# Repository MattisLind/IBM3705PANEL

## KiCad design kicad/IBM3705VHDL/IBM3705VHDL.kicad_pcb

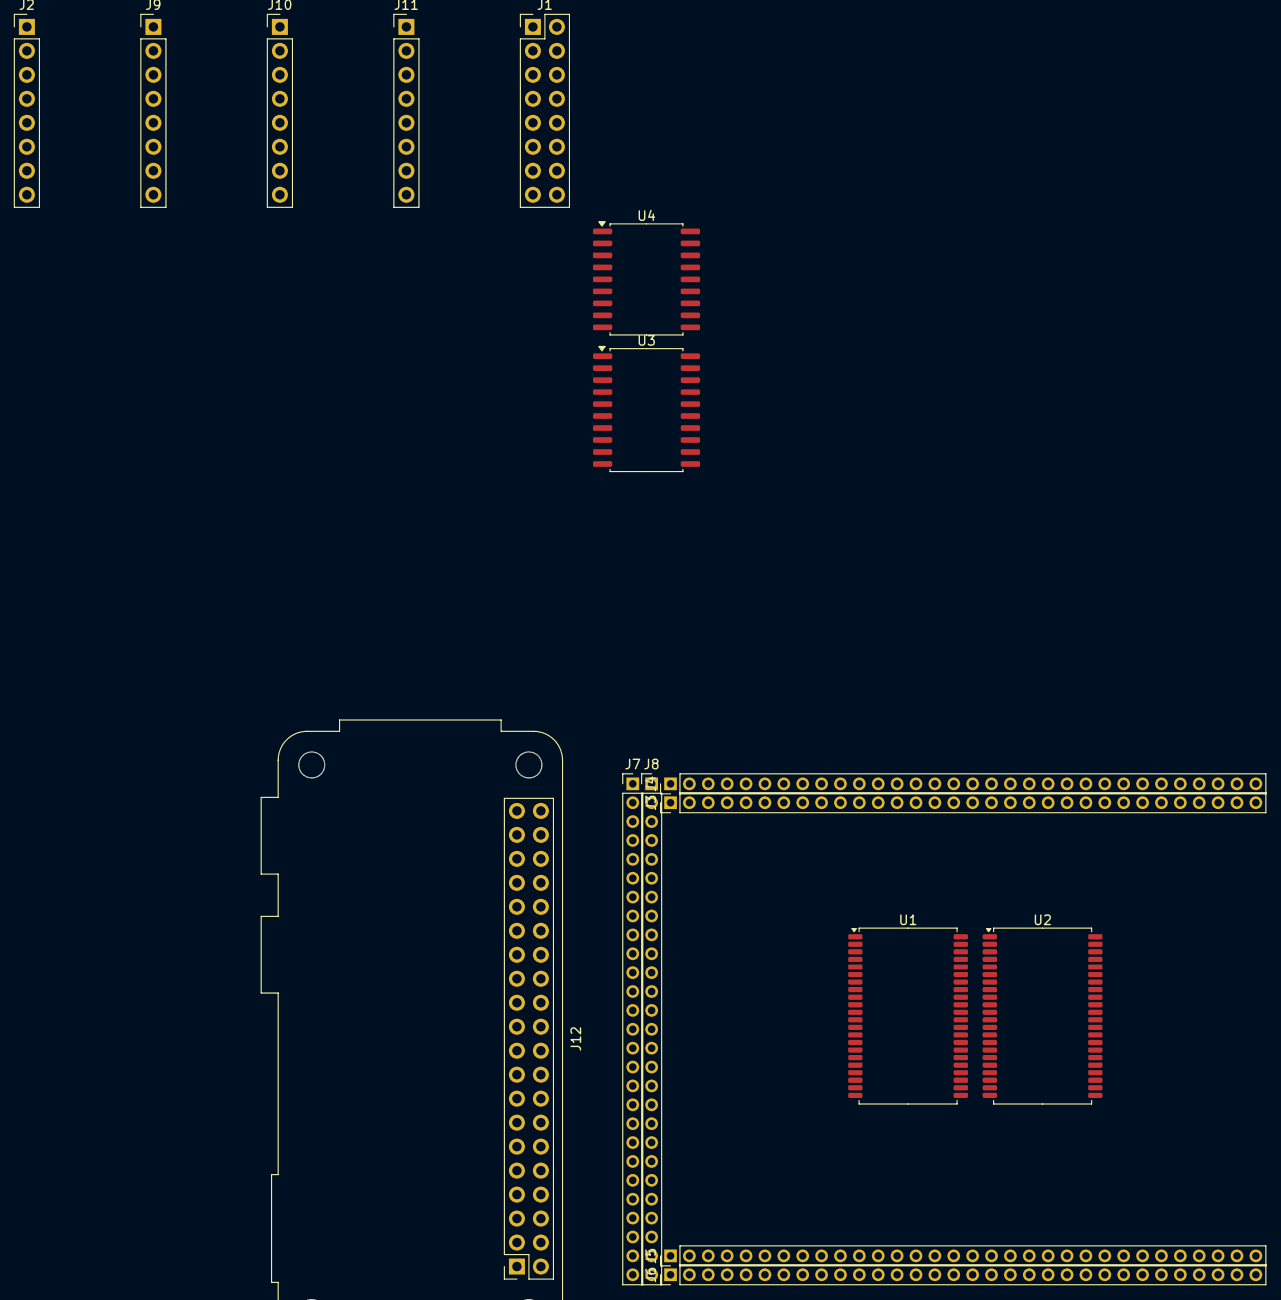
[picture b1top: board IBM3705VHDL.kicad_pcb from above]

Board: 2 copper layers, 16 parts (0 on the bottom side), 36 nets, no tracks yet.

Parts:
J1: Conn_02x08_Odd_Even; PinHeader_2x08_P2.54mm_Vertical
J2: Power; PinHeader_1x08_P2.54mm_Vertical
J3, J4, J5, J6: Conn_01x32; PinHeader_1x32_P2.00mm_Vertical
J7, J8: Conn_01x27; PinHeader_1x27_P2.00mm_Vertical
J9: 4V; PinHeader_1x08_P2.54mm_Vertical
J10: 6V; PinHeader_1x08_P2.54mm_Vertical
J11: 12V; PinHeader_1x08_P2.54mm_Vertical
J12: Raspberry_Pi_4; Raspberry_Pi_Zero_Socketed_THT_FaceDown_MountingHoles
U1, U2: IS64C5128AL-12CTLA3; TSOP-II-44_10.16x18.41mm_P0.8mm
U3: 74HC574; SOIC-20W_7.5x12.8mm_P1.27mm
U4: ULN2803A; SOIC-18W_7.5x11.6mm_P1.27mm

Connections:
+3V3: J5.30, J6.31
+4V: J9.1, J9.2, J9.3, J9.4, J9.5, J9.6, J9.7, J9.8
+6V: J10.1, J10.2, J10.3, J10.4, J10.5, J10.6, J10.7, J10.8
+12V: J11.1, J11.2, J11.3, J11.4, J11.5, J11.6, J11.7, J11.8
GND: J5.31, J6.32, U3.1 (OE), U3.10 (GND), U4.9 (GND)
unnamed: J1.1, U4.18 (O1)
unnamed: J1.2, J2.1
unnamed: J1.3, U4.17 (O2)
unnamed: J1.4, J2.2
unnamed: J1.5, U4.16 (O3)
unnamed: J1.6, J2.3
unnamed: J1.7, U4.15 (O4)
unnamed: J1.8, J2.4
unnamed: J1.9, U4.14 (O5)
unnamed: J1.10, J2.5
unnamed: J1.11, U4.13 (O6)
unnamed: J1.12, J2.6
unnamed: J1.13, U4.12 (O7)
unnamed: J1.14, J2.7
unnamed: J1.15, U4.11 (O8)
unnamed: J1.16, J2.8
unnamed: J12.1 (3V3), J12.17 (3V3)
unnamed: J12.2 (5V), J12.4 (5V)
unnamed: J12.6 (GND), J12.9 (GND), J12.14 (GND), J12.20 (GND), J12.25 (GND), J12.30 (GND), J12.34 (GND), J12.39 (GND)
unnamed: U1.12 (GND), U1.34 (GND)
unnamed: U1.11 (VDD), U1.33 (VDD)
unnamed: U2.12 (GND), U2.34 (GND)
unnamed: U2.11 (VDD), U2.33 (VDD)
unnamed: U3.19 (Q0), U4.1 (I1)
unnamed: U3.18 (Q1), U4.2 (I2)
unnamed: U3.17 (Q2), U4.3 (I3)
unnamed: U3.16 (Q3), U4.4 (I4)
unnamed: U3.15 (Q4), U4.5 (I5)
unnamed: U3.14 (Q5), U4.6 (I6)
unnamed: U3.13 (Q6), U4.7 (I7)
unnamed: U3.12 (Q7), U4.8 (I8)

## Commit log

2025-09-03 Added kicad files for the project.
